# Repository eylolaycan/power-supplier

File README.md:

# Breadboard Power Supply Module

A basic regulated power supply PCB designed for powering breadboard circuits with selectable 3.3V or 5V output.

## Features
- Designed in **KiCad 8**
- LM7805 voltage regulator (For 5V output)
- LM317 voltage regulator (For 3.3V output)
- Input via barrel jack
- Designed for direct insertion onto breadboard power rails

## Preview

## Status
- [x] Schematic complete
- [x] PCB layout complete
- [x] Gerber export
- [ ] Assembly and testing

## Purpose
Designed based on what I learned from The Complete Electronics: Analog Hardware Design course, and inspired by existing power supply modules I had on hand. This project helped reinforce my understanding of analog power regulation and practical PCB layout techniques.

## License
MIT

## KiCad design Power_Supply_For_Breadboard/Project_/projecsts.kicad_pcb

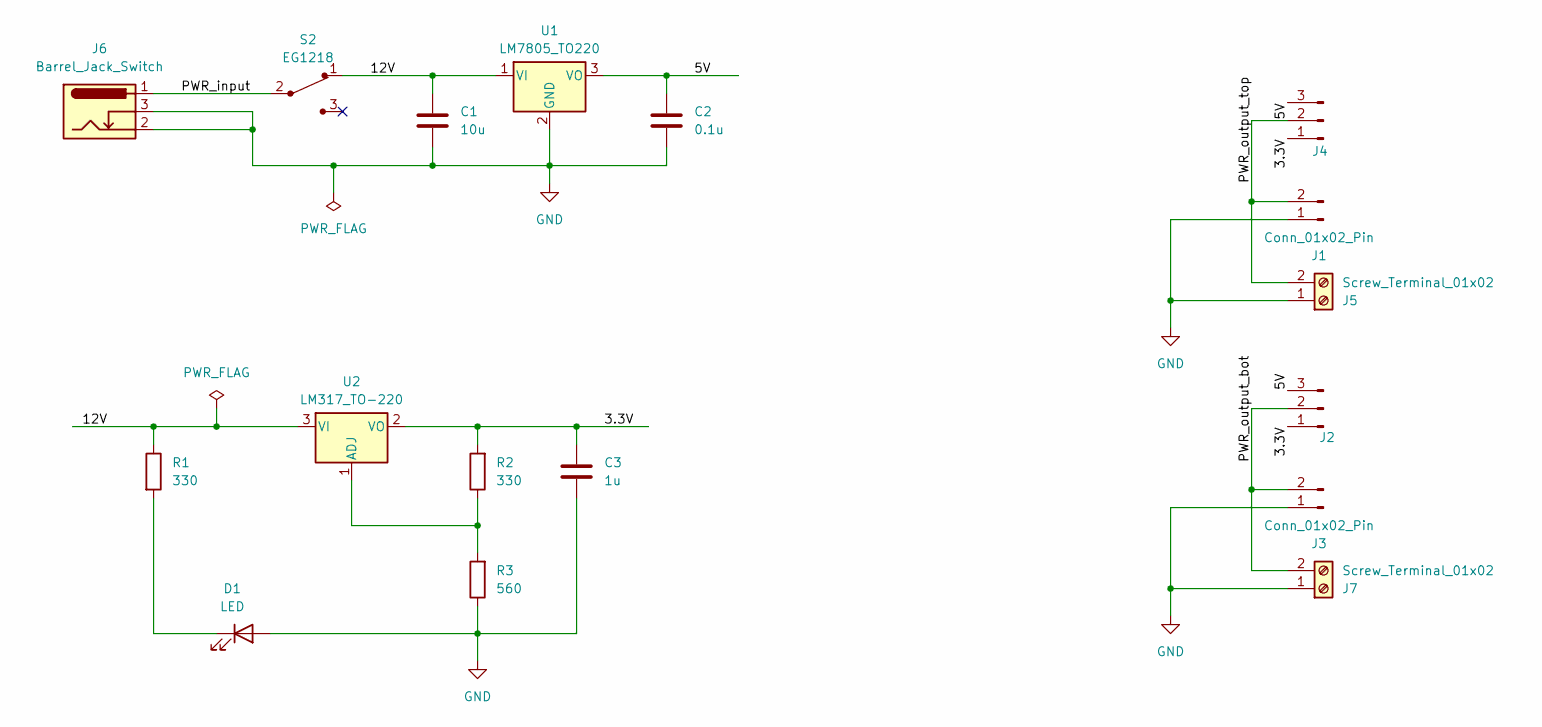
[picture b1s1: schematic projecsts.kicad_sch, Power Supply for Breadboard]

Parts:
C1: 10u; C_Disc_D3.0mm_W1.6mm_P2.50mm
C2: 0.1u; C_Disc_D3.0mm_W1.6mm_P2.50mm
C3: 1u; C_Disc_D3.0mm_W1.6mm_P2.50mm
D1: LED; LED_D5.0mm
J1, J3: Conn_01x02_Pin; PinHeader_2x01_P2.54mm_Vertical
J2, J4: Conn_01x03_Pin; PinHeader_1x03_P2.54mm_Vertical
J5, J7: Screw_Terminal_01x02; TerminalBlock_bornier-2_P5.08mm
J6: Barrel_Jack_Switch; BarrelJack_Horizontal
R1, R2: 330; R_Axial_DIN0204_L3.6mm_D1.6mm_P7.62mm_Horizontal
R3: 560; R_Axial_DIN0204_L3.6mm_D1.6mm_P7.62mm_Horizontal
S2: EG1218; Switch_Slide_11.6x4mm_EG1218; MPN EG1218; Digi-Key_PN EG1903-ND
U1: LM7805_TO220; TO-220-3_Vertical
U2: LM317_TO-220; TO-220-3_Vertical

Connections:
/3.3V: C3.1, J2.1, J4.1, R2.2, U2.2 (VO)
/5V: C2.1, J2.3, J4.3, U1.3 (VO)
/12V: C1.1, R1.1, S2.1, U1.1 (VI), U2.3 (VI)
/PWR_input: J6.1, S2.2
/PWR_output_bot: J2.2, J3.2, J7.2
/PWR_output_top: J1.2, J4.2, J5.2
GND: C1.2, C2.2, C3.2, D1.2 (A), J1.1, J3.1, J5.1, J6.2, J6.3, J7.1, R3.1, U1.2 (GND)
unnamed: D1.1 (K), R1.2
unnamed: R2.1, R3.2, U2.1 (ADJ)

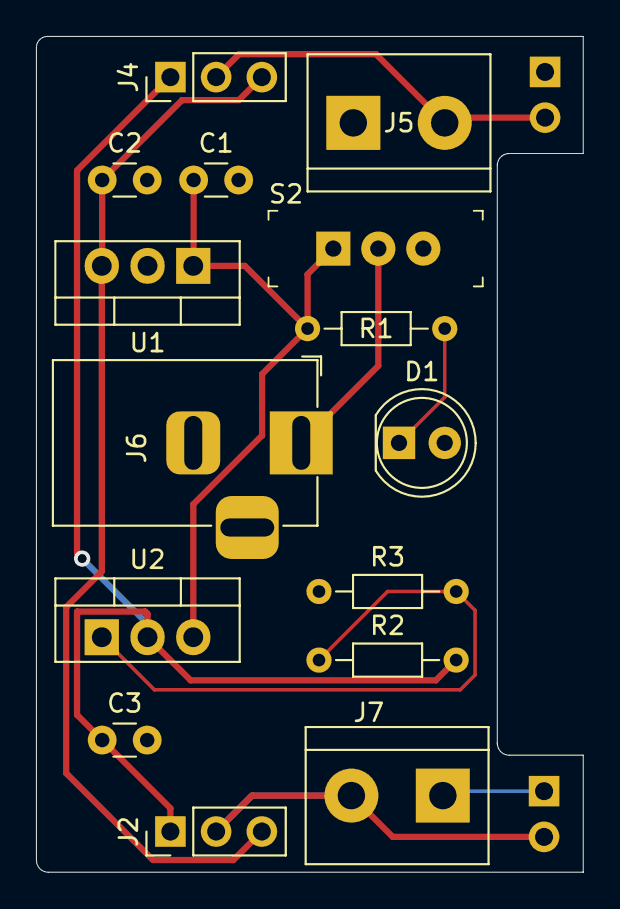
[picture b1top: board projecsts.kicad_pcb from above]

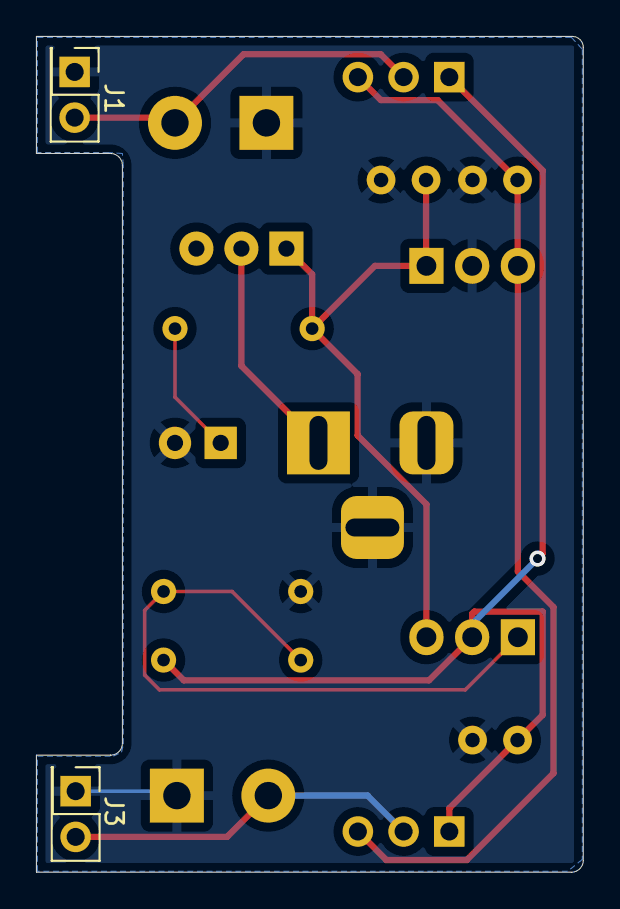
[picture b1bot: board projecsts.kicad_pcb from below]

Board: 2 copper layers, 30.4 x 46.4 mm, 17 parts (2 on the bottom side), 9 nets.

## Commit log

2025-03-22 Update README.md
    editted for more knowledge
2025-03-22 add image via upload
2025-03-22 Create Project_KiCad
2025-03-23 Initial commit for power supply project.
2025-03-23 Create README.md
    correct
2025-03-23 upload images
2025-03-23 Update README.md
    correct
2025-03-23 Update README.md
    try to fix image
2025-03-23 Update README.md
    fix image
